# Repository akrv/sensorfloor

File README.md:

# sensorfloor

Management software for PhyNetLab: sensor floor

```
sudo apt-get install git python-pip owfs python-ow ow-shell
```

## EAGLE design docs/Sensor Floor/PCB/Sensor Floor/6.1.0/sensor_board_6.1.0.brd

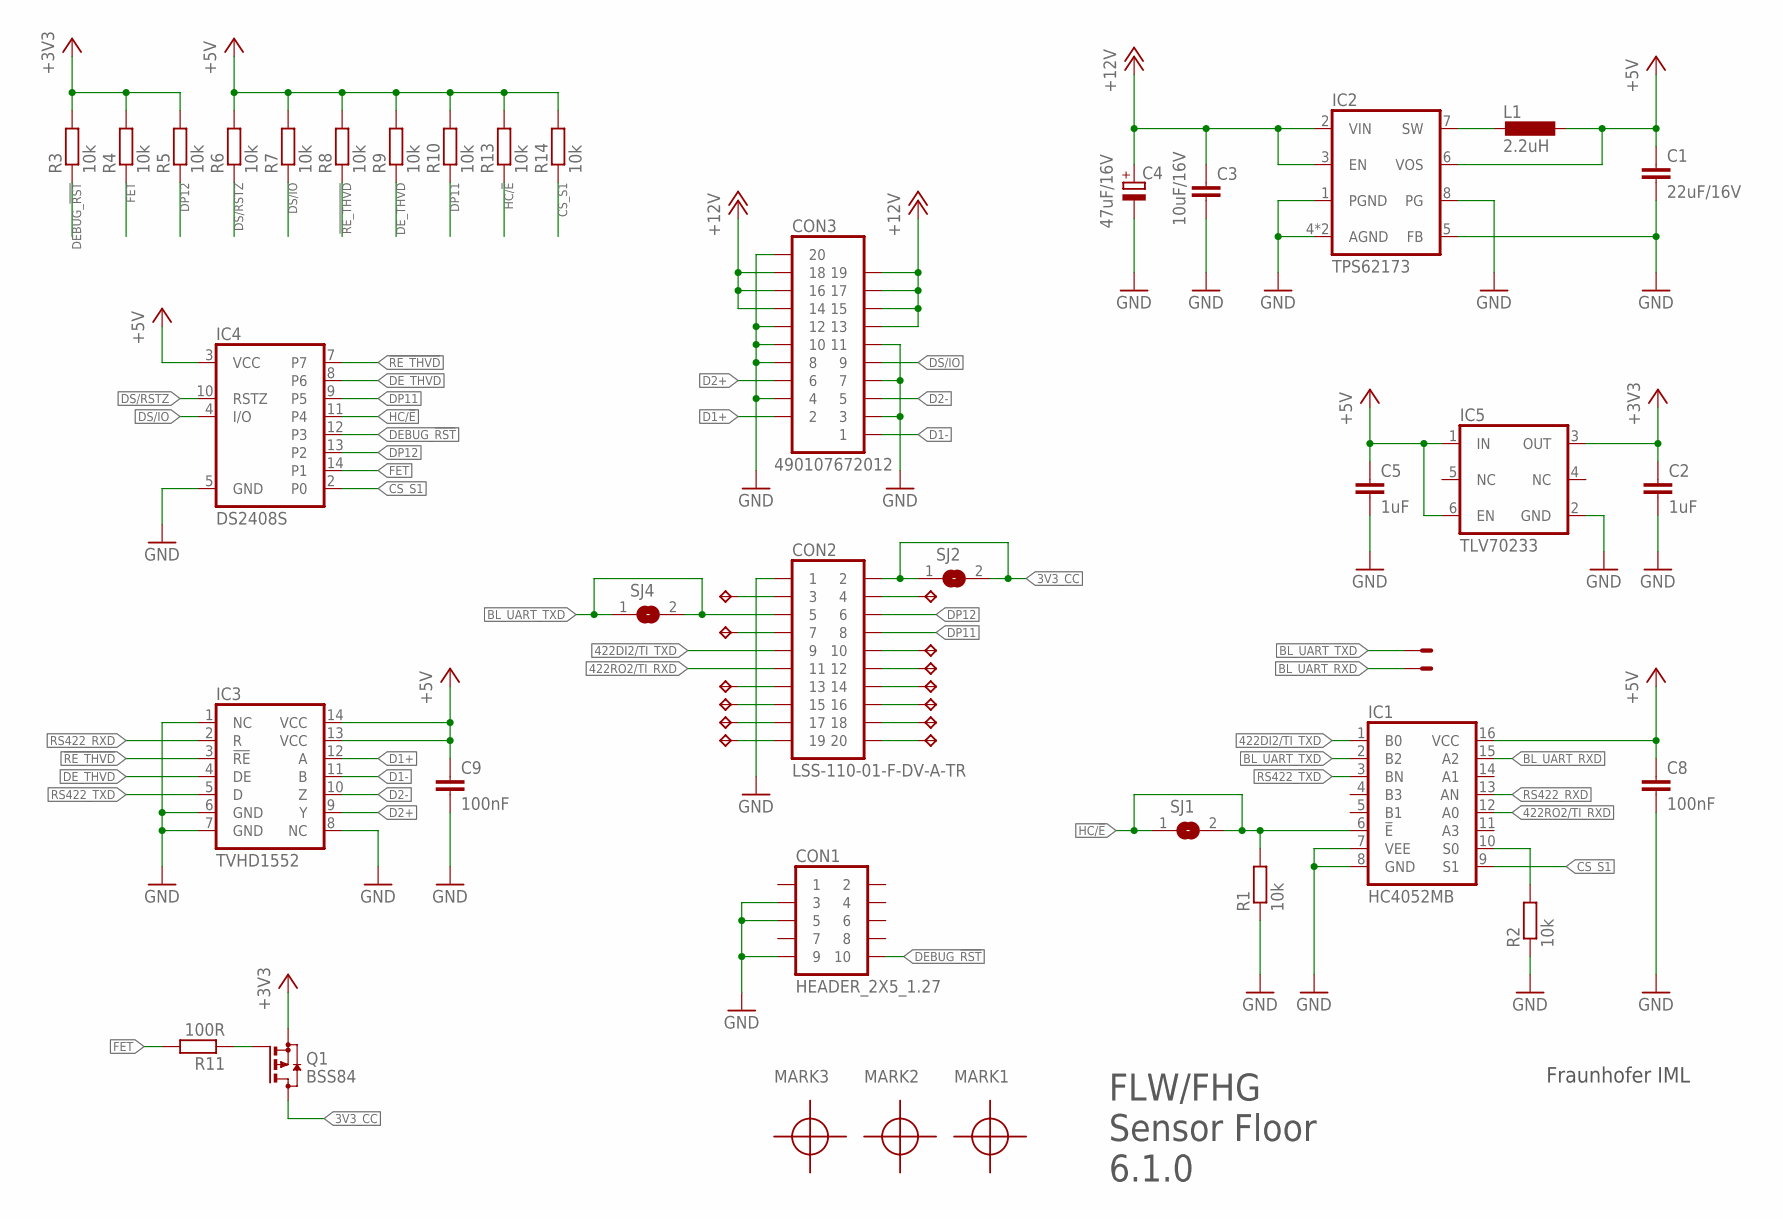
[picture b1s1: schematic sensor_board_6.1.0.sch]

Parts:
C1: 22uF/16V; C0805K
C2, C5: 1uF; C0603
C3: 10uF/16V; C0805K
C4: 47uF/16V; C/6032-28R
C8, C9: 100nF; C0402
CON1: HEADER_2X5_1.27
CON2: LSS-110-01-F-DV-A-TR
CON3: 490107672012
IC1: HC4052MB; SO16
IC2: TPS62173; WSON8
IC3: TVHD1552; SO14
IC4: DS2408S; SO16
IC5: TLV70233; S-PDSO-N6
L1: 2.2uH; L-1212FPS_SHIELDED
MARK1, MARK2, MARK3: PASSMARK
Q1: BSS84; SOT23
R1, R2, R3, R4, R5, R6, R7, R8, R9, R10, R13, R14: 10k; R0402
R11: 100R; R0402
SJ1, SJ2, SJ4: SJT
TP1, TP4: TP/SP-1.5X1.0; SOLDERPAD_1.5X1.0
TP2, TP3, TP5, TP6, TP7, TP8, TP9, TP10, TP11, TP12, TP13, TP14, TP15: TPTP08R; TP08R

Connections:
3V3_CC: CON2.P2 (2), Q1.3 (D), SJ2.1, SJ2.2
422DI2/TI_TXD: CON2.P9 (9), IC1.1 (B0)
422RO2/TI_RXD: CON2.P11 (11), IC1.12 (A0)
!RE_THVD: IC3.3 (!RE), IC4.7, R8.P$1 (1)
+3V3: C2.1, IC5.3 (OUT), Q1.2 (S), R3.P$2 (2), R4.P$2 (2), R5.P$2 (2)
+5V: C1.1, C5.1, C8.P$1 (1), C9.P$1 (1), IC1.16 (VCC), IC2.6 (VOS), IC3.13 (VCC), IC3.14 (VCC), IC4.3 (VCC), IC5.1 (IN), IC5.6 (EN), L1.1, R6.P$2 (2), R7.P$2 (2), R8.P$2 (2), R9.P$2 (2), R10.P$2 (2), R13.P$2 (2), R14.P$2 (2)
+12V: C3.1, C4.+, CON3.13, CON3.14, CON3.15, CON3.16, CON3.17, CON3.18, CON3.19, IC2.2 (VIN), IC2.3 (EN)
BL_UART_RXD: IC1.15 (A2), TP4.1
BL_UART_TXD: CON2.P5 (5), IC1.2 (B2), SJ4.1, SJ4.2, TP1.1
CS_S1: IC1.9 (S1), IC4.2 (P0), R14.P$1 (1)
D1+: CON3.2, IC3.12 (A)
D1-: CON3.1, IC3.11 (B)
D2+: CON3.6, IC3.9 (Y)
D2-: CON3.5, IC3.10 (Z)
DEBUG_!RST: CON1.P$10 (10), IC4.12 (P3), R3.P$1 (1)
DE_THVD: IC3.4 (DE), IC4.8 (P6), R9.P$1 (1)
DP11: CON2.P8 (8), IC4.9 (P5), R10.P$1 (1)
DP12: CON2.P6 (6), IC4.13 (P2), R5.P$1 (1)
DS/IO: CON3.9, IC4.4 (I/O), R7.P$1 (1)
DS/RSTZ: IC4.10 (RSTZ), R6.P$1 (1)
FET: IC4.14 (P1), R4.P$1 (1), R11.P$2 (2)
GND: C1.2, C2.2, C3.2, C4.-, C5.2, C8.P$2 (2), C9.P$2 (2), CON1.P$3 (3), CON1.P$5 (5), CON1.P$9 (9), CON2.P1 (1), CON3.3, CON3.4, CON3.7, CON3.8, CON3.10, CON3.11, CON3.12, CON3.20, IC1.7 (VEE), IC1.8 (GND), IC2.1 (PGND), IC2.4 (AGND), IC2.5 (FB), IC2.8 (PG), IC2.EXP (AGND), IC3.1 (NC), IC3.6 (GND), IC3.7 (GND), IC3.8 (NC), IC4.5 (GND), IC5.2 (GND), R1.P$1 (1), R2.P$1 (1)
HC/!E: IC1.6 (!E), IC4.11 (P4), R1.P$2 (2), R13.P$1 (1), SJ1.1, SJ1.2
unnamed: CON2.P10 (10), TP3.TP
unnamed: Q1.1 (G), R11.P$1 (1)
unnamed: IC1.10 (S0), R2.P$2 (2)
unnamed: IC2.7 (SW), L1.2
unnamed: CON2.P12 (12), TP2.TP
unnamed: CON2.P14 (14), TP5.TP
unnamed: CON2.P16 (16), TP6.TP
unnamed: CON2.P18 (18), TP7.TP
unnamed: CON2.P20 (20), TP8.TP
unnamed: CON2.P19 (19), TP9.TP
unnamed: CON2.P17 (17), TP10.TP
unnamed: CON2.P15 (15), TP11.TP
unnamed: CON2.P13 (13), TP12.TP
unnamed: CON2.P7 (7), TP13.TP
unnamed: CON2.P4 (4), TP14.TP
unnamed: CON2.P3 (3), TP15.TP
RS422_RXD: IC1.13 (AN), IC3.2 (R)
RS422_TXD: IC1.3 (BN), IC3.5 (D)

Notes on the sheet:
FLW/FHG Sensor Floor 6.1.0
Fraunhofer IML

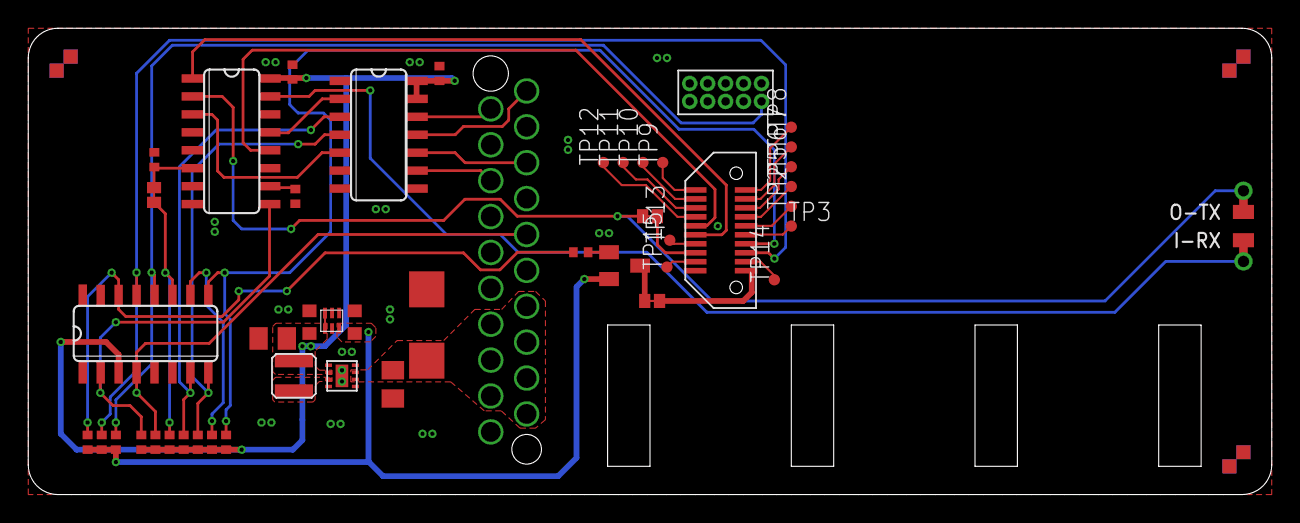
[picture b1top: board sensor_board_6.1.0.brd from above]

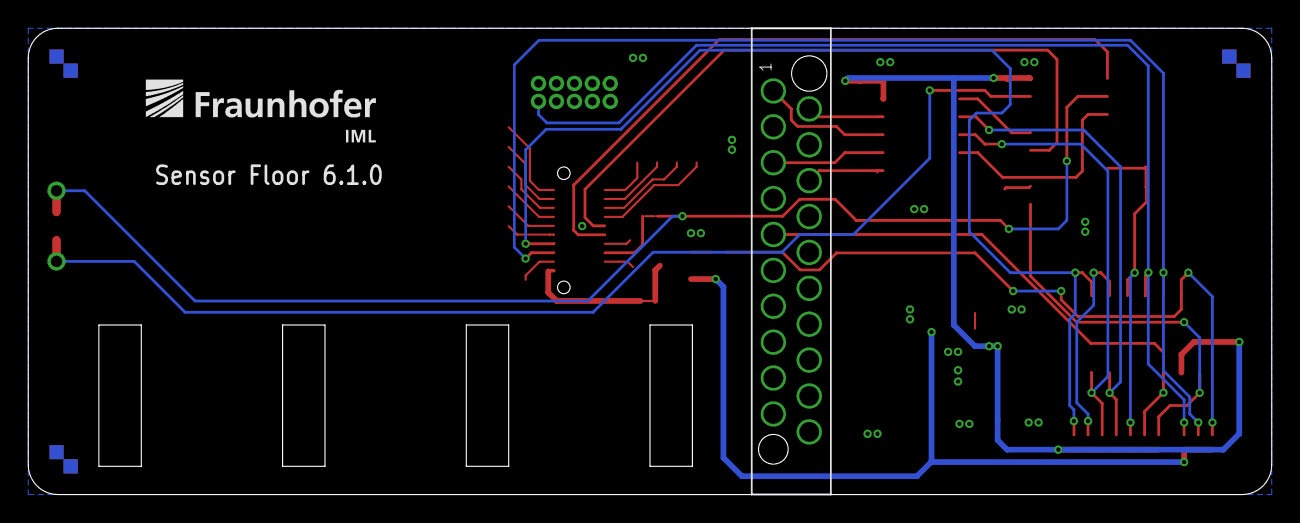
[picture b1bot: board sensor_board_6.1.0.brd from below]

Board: 2 copper layers, 88.0 x 33.0 mm, 52 parts (2 on the bottom side), 41 nets.

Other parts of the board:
U$2: IML_0.13_TPLACE

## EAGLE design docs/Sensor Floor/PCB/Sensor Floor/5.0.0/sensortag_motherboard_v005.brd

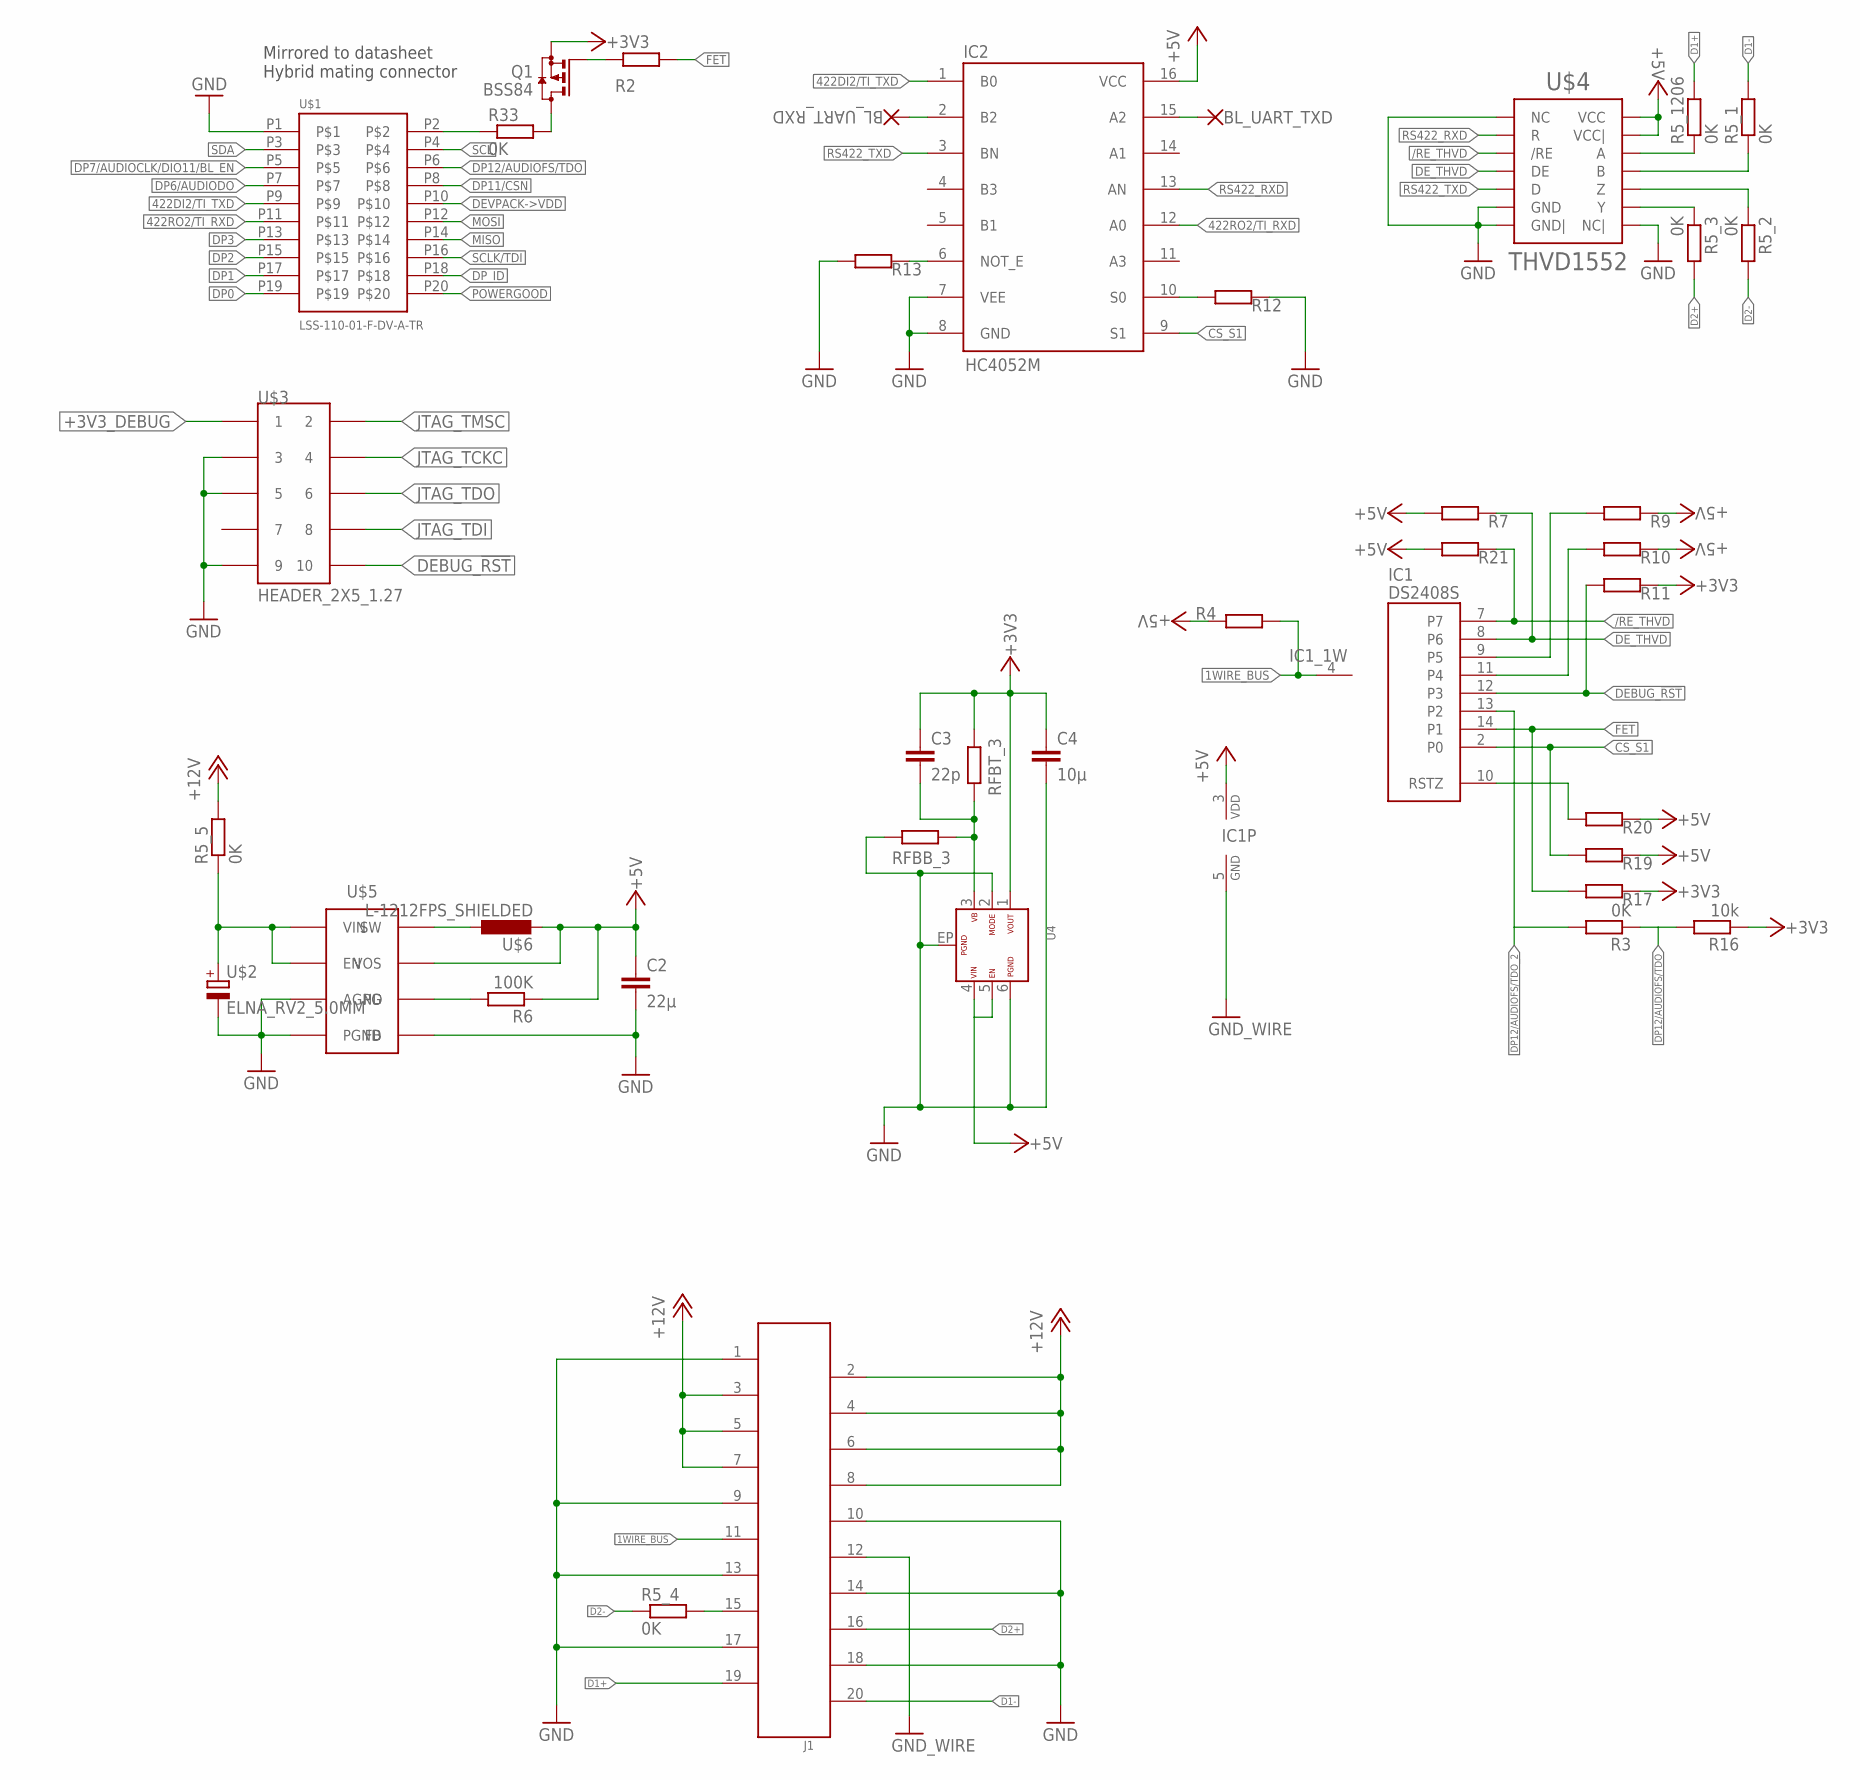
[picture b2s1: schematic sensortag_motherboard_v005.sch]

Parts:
BL_UART_RXD: WIREPADSMD1,27-254; SMD1,27-2,54
BL_UART_TXD: WIREPADSMD1,27-254; SMD1,27-2,54
C2: 22µ; C1210
C3: 22p; C0402
C4: 10µ; C0603
IC1: DS2408S; SO16
IC2: HC4052M; SO16
J1: 490107672012
Q1: BSS84; SOT23
R2: 100; R0402
R3, R33: 0K; R0603
R4, R7, R9, R10, R11, R12, R13, R16, R17, R19, R20, R21: 10k; R0402
R5_1, R5_2, R5_3, R5_4, R5_5, R5_1206: 0K; R1206
R6: 100K; R0603
RFBB_3: 22,1K; R0402
RFBT_3: 100K; R0402
U4: VDMM_171960501
U$1: LSS-110-01-F-DV-A-TR
U$2: ELNA_RV2_5.0MM
U$3: HEADER_2X5_1.27
U$4: TVHD1552; SO14
U$5: TPS62173; WSON8
U$6: L-1212FPS_SHIELDED

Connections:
1WIRE_BUS: IC1.4 (1W), J1.11 (10), R4.P$2 (2)
422DI2/TI_TXD: IC2.1 (B0), U$1.P9
422RO2/TI_RXD: IC2.12 (A0), U$1.P11
+3V3: C3.1, C4.1, Q1.2 (S), R11.P$1 (1), R16.P$1 (1), R17.P$1 (1), RFBT_3.P$1 (1), U4.1 (VOUT)
+3V3_DEBUG: U$3.P$1 (1)
+5V: C2.1, IC1.3 (VDD), IC2.16 (VCC), R4.P$1 (1), R6.1, R7.P$2 (2), R9.P$1 (1), R10.P$1 (1), R19.P$1 (1), R20.P$1 (1), R21.P$2 (2), U4.4 (VIN), U4.5 (EN), U$4.13 (VCC|), U$4.14 (VCC), U$5.VOS, U$6.P$2 (2)
+12V: J1.2 (19), J1.3 (18), J1.4 (17), J1.5 (16), J1.6 (15), J1.7 (14), J1.8 (13), R5_5.2
/RE_THVD: IC1.7, R21.P$1 (1), U$4.3 (/RE)
BL_UART_RXD: BL_UART_RXD.1, IC2.2 (B2)
BL_UART_TXD: BL_UART_TXD.1, IC2.15 (A2)
CS_S1: IC1.2 (P0), IC2.9 (S1), R19.P$2 (2)
D1+: J1.19 (2), R5_1206.2
D1-: J1.20 (1), R5_1.2
D2+: J1.16 (5), R5_3.2
D2-: R5_2.2, R5_4.1
DEBUG_!RST: IC1.12 (P3), R11.P$2 (2), U$3.P$10 (10)
DEVPACK->VDD: U$1.P10
DE_THVD: IC1.8 (P6), R7.P$1 (1), U$4.4 (DE)
DP0: U$1.P19
DP1: U$1.P17
DP2: U$1.P15
DP3: U$1.P13
DP6/AUDIODO: U$1.P7
DP7/AUDIOCLK/DIO11/BL_EN: U$1.P5
DP11/CSN: U$1.P8
DP12/AUDIOFS/TDO: R3.1, R16.P$2 (2), U$1.P6
DP12/AUDIOFS/TDO_2: IC1.13 (P2), R3.2
DP_ID: U$1.P18
DS4: IC1.11 (P4), R10.P$2 (2)
DS5: IC1.9 (P5), R9.P$2 (2)
DS_RESET: IC1.10 (RSTZ), R20.P$2 (2)
FET: IC1.14 (P1), R2.P$1 (1), R17.P$2 (2)
GND: C2.2, C4.2, IC2.7 (VEE), IC2.8 (GND), J1.1 (20), J1.9 (12), J1.10 (11), J1.13 (8), J1.14 (7), J1.17 (4), J1.18 (3), R12.P$1 (1), R13.P$2 (2), RFBB_3.P$2 (2), U4.2 (MODE), U4.6 (PGND), U4.EP (PGND1), U$1.P1, U$2.P- (-), U$3.P$3 (3), U$3.P$5 (5), U$3.P$9 (9), U$4.1 (NC), U$4.6 (GND), U$4.7 (GND|), U$4.8 (NC|), U$5.AGND, U$5.AGND2 (AGND), U$5.FB, U$5.PGND
GND_WIRE: IC1.5 (GND), J1.12 (9)
JTAG_TCKC: U$3.P$4 (4)
JTAG_TDI: U$3.P$8 (8)
JTAG_TDO: U$3.P$6 (6)
JTAG_TMSC: U$3.P$2 (2)
MISO: U$1.P14
MOSI: U$1.P12
unnamed: R33.1, U$1.P2
unnamed: Q1.3 (D), R33.2
unnamed: Q1.1 (G), R2.P$2 (2)
unnamed: R6.2, U$5.PG
unnamed: C3.2, RFBB_3.P$1 (1), RFBT_3.P$2 (2), U4.3 (FB)
unnamed: R5_1206.1, U$4.12 (A)
unnamed: R5_1.1, U$4.11 (B)
unnamed: R5_2.1, U$4.10 (Z)
unnamed: R5_3.1, U$4.9 (Y)
unnamed: R5_5.1, U$2.P+ (+), U$5.EN, U$5.VIN
unnamed: U$5.SW, U$6.P$1 (1)
unnamed: J1.15 (6), R5_4.2
unnamed: IC2.10 (S0), R12.P$2 (2)
POWERGOOD: U$1.P20
PULLDOWN_???: IC2.6 (NOT_E), R13.P$1 (1)
RS422_RXD: IC2.13 (AN), U$4.2 (R)
RS422_TXD: IC2.3 (BN), U$4.5 (D)
SCL: U$1.P4
SCLK/TDI: U$1.P16
SDA: U$1.P3

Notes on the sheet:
Mirrored to datasheet Hybrid mating connector

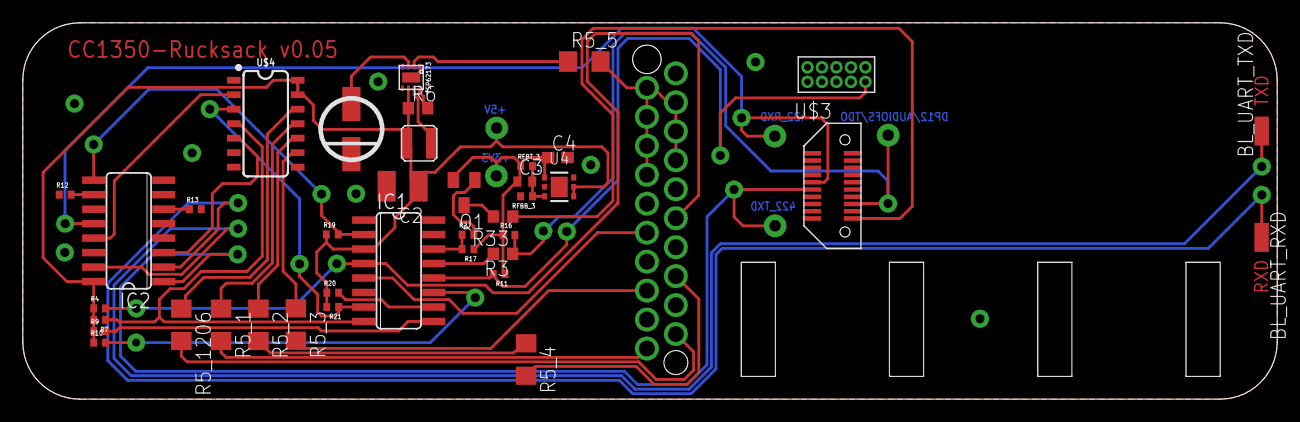
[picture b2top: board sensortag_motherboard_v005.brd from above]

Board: 2 copper layers, 110.0 x 33.0 mm, 40 parts (1 on the bottom side), 40 nets.

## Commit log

2019-05-30 ignoring IDE settings
2019-05-30 How to use lightfinder
2019-05-30 pushing commented code
2019-05-30 typo
2019-05-30 adding video to repo
2019-06-10 wrapper and flask, initial commit
2019-06-10 RPi GPIO 4 direct drive
2019-06-10 frontend page added with interesting information
2019-08-01 documentation for bootloader settings
2019-08-01 documentation of the PCB
2019-08-06 addr finder prints out errors and findouts.
2019-08-06 hex files and added documentation
2019-08-06 typo fixed
2019-08-06 check if all 1wire nodes are available in the bus
2019-08-06 addr_finder docs in the right place
2019-08-16 modal created for view and edit boxes
2019-08-21 edit modal edited
2019-08-21 showing progress while running
2019-08-21 address finder integrated to REST_API
2019-08-22 address finder is complete as a module
2019-08-22 template fixed with a list and the first index is 0
2019-08-22 addr_finder and node view fixed
2019-08-22 file upload with device ID fixed
2019-08-23 toggle pin API implemented, tested
2019-08-23 write only if errors are passed
2019-08-23 toggle API function works.
2019-08-23 read data for line and event based. line is done, event is not
2019-10-22 added application (written with TI-RTOS) to print imu data when interrupt is set at DP12 (IOID_16)
2019-10-23 code cleanup and added app hex file (imu_data_interrupt.out)
2019-11-08 test stand version
2019-11-08 installation update
2019-11-09 adding support for reading file
2019-11-09 formating main readme.md
2019-11-09 adding pip dependencies
2019-11-09 Bump pyxdg from 0.25 to 0.26
    Bumps [pyxdg](https://github.com/takluyver/pyxdg) from 0.25 to 0.26.
    - [Release notes](https://github.com/takluyver/pyxdg/releases)
    - [Changelog](https://github.com/takluyver/pyxdg/blob/master/ChangeLog)
    - [Commits](https://github.com/takluyver/pyxdg/compare/rel-0.25...rel-0.26)
2019-11-18 adding force_find parameter
2019-11-18 adding arg parse to force
2019-11-18 added sleep iterating through strip to flash
2019-11-18 setting to bootloader mode from front end. jelmer needs to flash now
2019-11-19 flashing is not working because of the file format of the hex files.
2019-11-19 updated hex files
2019-11-19 remove old hex files
2019-11-21 added .bin file, updated .out and .hex
2019-11-22 homepage footer fix - not working
2019-11-23 reading IMU data and publishing in MQTT
2019-11-23 flashing for all devices testing and working
2019-11-23 comments for some lunacy
2019-11-23 function ready to be used from another program
2019-11-23 latency specific to device
2019-11-25 reading and real time plotter
2019-11-26 collecting data for 1 device by sensor._path value
2019-11-26 latency calculation
2019-11-26 latency corrected
2019-11-26 readme with latency times
2019-11-26 added line breakˆ
2019-11-27 updated timing
2019-11-27 write to file updated
2019-11-27 time calculation corrected.
2019-12-06 edited imu app to print in json format (buffer imu 28 readings at 7 hz)
2019-12-09 live plotter at gyro data
2019-12-09 indexing error with one off. corrected with -1
2019-12-11 fixed bug in imu app
2019-12-11 change printing format to binary
2019-12-13 changed imu app, added python script to read it
2019-12-13 fixed bug in mag
2019-12-13 turn off after flashing, parsing bin data
2019-12-13 increase baud rate
2019-12-17 tryouts current state
2019-12-17 add .bin for imu app with 921600
2019-12-17 changed imu_app interrupt logic
2019-12-17 small change to imu_app
2019-12-18 floor deploying commands
2019-12-18 conf file updated
2019-12-18 copy addr to github gists
2019-12-18 indexing for username and password changed
2019-12-18 node order json files with respective names. RPi 6 is pending
2019-12-19 6th Pi also added, with new IP address
2019-12-19 flashing all nodes with a POST req. Pi 6 has new ip addr
2019-12-19 ip addresses removed from repo
2019-12-19 import fixed
2019-12-19 read all messages from all devices
2019-12-19 flashfloor.py flashes all PIs, sensorfloor.py works with wsgi
2019-12-19 fabfile knows to add flash folder at the right place
2019-12-19 changed mqtt client ID
2019-12-19 live plotted added with RPi IPS, todo: import not working
2019-12-19 improving deploy automation
2019-12-19 adding more info to stats
2019-12-19 debugging strip 23 dev 5
2019-12-19 another dead sensor added to reading
2019-12-19 added the right command to run reader, but now commandline needs to be active
2019-12-20 python file for position from vicon
2019-12-20 with correct filename
2019-12-20 adding test data from vicon and mqtt
2019-12-20 adding documentation for the files
2019-12-20 adding documentation for the files: typo
2019-12-20 fixed
2020-01-08 fixing data collection issue with samples being overwritten to the same value
2020-02-24 changes made from hall computer: fix vicon msg, correct imports
2020-03-02 keep data raw
2020-04-28 fix wrong order of buffer flushing of sensors data
2020-05-01 add RSSI data to floor firmware
2020-05-04 add robot tx firmware, use events to update rssi firmware
2020-05-11 handle magnetometer error flags, add firmware bin files
2020-05-15 recompile and convert floor firmware with same compiler version
2020-05-15 collect RSSI readings from the python script on RPI
2020-05-15 Handle broken nodes
2020-05-18 live plotter fixed to take data from node_id 1 as well
2020-05-25 add script to turn on/off power and rss-422
2020-05-25 edit flashing script to flash a single node
2020-05-27 add script to log serial data
2020-06-08 publishing in another namespace to improve redis access
2020-06-08 namespace issues
2020-06-08 column_num referenced
2020-06-08 column_num int to str cast
2020-06-08 strip_id missed in a spot. now added as well
2020-06-08 updating str comparison for macid
2020-06-08 summerschool server
2020-06-08 authentication server
2020-06-08 print statement removed
2020-06-15 changing requirements for security vulnerabilities
2020-06-17 route for requesting robot actions is implemented
2020-06-17 readme updated with documentation
2020-06-23 add robot control API to summerschool
2020-07-28 fixing summer school robot navigation APIs
2020-08-19 Handle robot status for summer school code
2020-08-19 current_values changed to read frame generation
2020-08-19 updated to listen on all interfaces
2020-08-26 Add summer school hackathon example
2020-08-26 readme updated with summer school documentation
2020-08-26 link updated for the example file
2020-08-26 Add feedback msgs for summerschool
2020-08-27 add server to give feedback about waypoints
2020-08-27 added waypoints API to summerschool server
2020-08-28 Add waypoints feedback to summerschool example
2020-09-03 fix waiting for robot feedback
2020-10-10 async implementation to flashfloor at the same time.
2020-10-12 print responses not only the status
2020-10-12 trying out post async. can use this in future for sending concurrent post or get requests.
2020-10-15 adding data and files.
2020-10-15 working with data having file and payload info of device.
2020-10-15 code formatted for spacing
2020-10-27 Bump cryptography from 2.6.1 to 3.2
    Bumps [cryptography](https://github.com/pyca/cryptography) from 2.6.1 to 3.2.
    - [Release notes](https://github.com/pyca/cryptography/releases)
    - [Changelog](https://github.com/pyca/cryptography/blob/master/CHANGELOG.rst)
    - [Commits](https://github.com/pyca/cryptography/compare/2.6.1...3.2)
2021-02-10 Bump cryptography from 3.2 to 3.3.2
    Bumps [cryptography](https://github.com/pyca/cryptography) from 3.2 to 3.3.2.
    - [Release notes](https://github.com/pyca/cryptography/releases)
    - [Changelog](https://github.com/pyca/cryptography/blob/master/CHANGELOG.rst)
    - [Commits](https://github.com/pyca/cryptography/compare/3.2...3.3.2)
2021-03-20 Bump jinja2 from 2.10.3 to 2.11.3
    Bumps [jinja2](https://github.com/pallets/jinja) from 2.10.3 to 2.11.3.
    - [Release notes](https://github.com/pallets/jinja/releases)
    - [Changelog](https://github.com/pallets/jinja/blob/master/CHANGES.rst)
    - [Commits](https://github.com/pallets/jinja/compare/2.10.3...2.11.3)
2021-03-25 Bump pyyaml from 5.1.2 to 5.4
    Bumps [pyyaml](https://github.com/yaml/pyyaml) from 5.1.2 to 5.4.
    - [Release notes](https://github.com/yaml/pyyaml/releases)
    - [Changelog](https://github.com/yaml/pyyaml/blob/master/CHANGES)
    - [Commits](https://github.com/yaml/pyyaml/compare/5.1.2...5.4)

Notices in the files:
parts and their libraries:
Eagle_STEP-DOWN-CONVERTER: Copyright: Würth Elektronik
